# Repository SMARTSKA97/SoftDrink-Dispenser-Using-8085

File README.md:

# SoftDrink-Dispenser-Using-8085
## Objective:
The basic idea of the automated Softdrink dispenser is that it allows the user to select one out of
three options (small, medium and large) for the amount of liquid as desired.

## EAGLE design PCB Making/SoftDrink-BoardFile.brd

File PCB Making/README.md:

This directory contains the construction of PCB using EAGLE Autodesk free version.
## Board Size
### Width = 
6.02 inches
### Height = 
3.85 inches

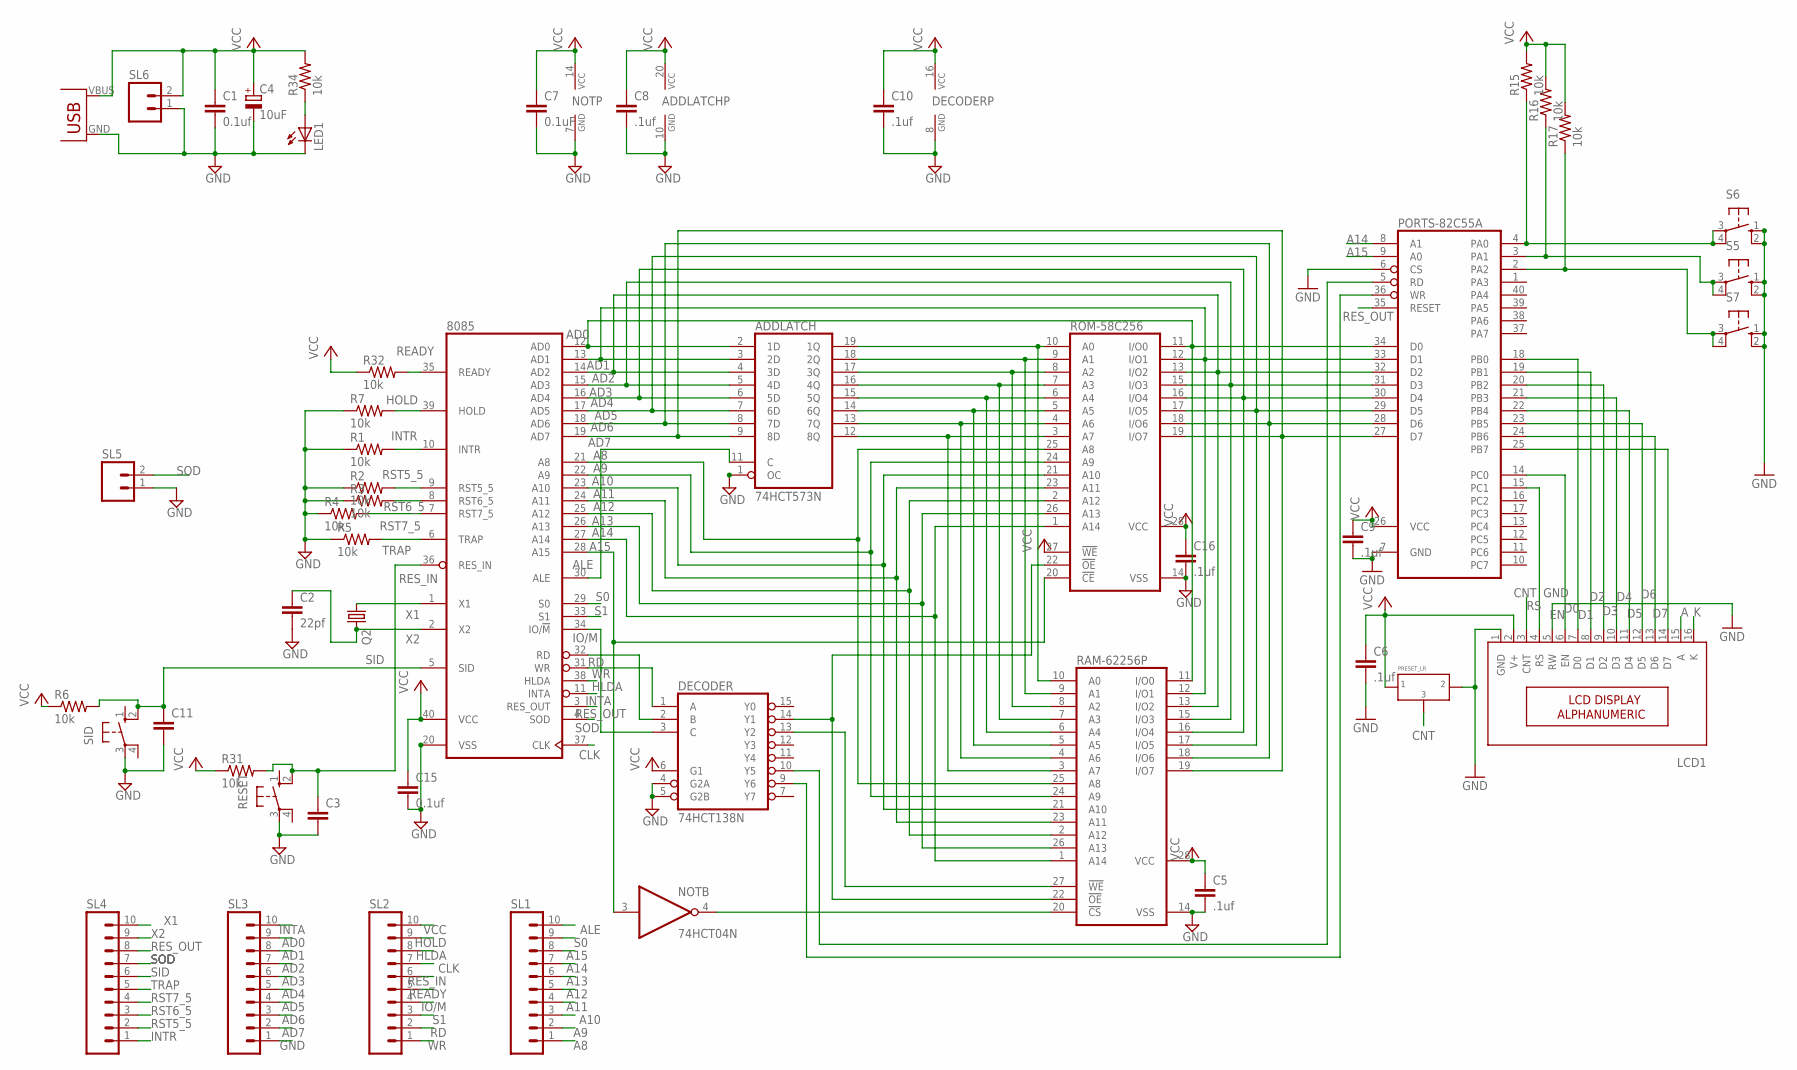
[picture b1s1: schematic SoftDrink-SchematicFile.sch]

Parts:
8085: 8085; DIL40
ADDLATCH: 74HCT573N; DIL20
C1, C15: 0.1uf; C025-024X044
C2: 22pf; C025-024X044
C3, C11: C-EU025-025X050; C025-025X050
C4: 10uF; E5-8,5
C5, C6, C8, C9, C10, C16: .1uf; C025-024X044
C7: 0.1uF; C025-024X044
DECODER: 74HCT138N; DIL16
LCD1: 16X2LCD; 16X2_LCD
LED1: LED5MM
NOT: 74HCT04N; DIL14
PORTS-82C55A: 82C55A; DIL40
Q2: CRYSTALHC49US; HC49US
R1, R2, R3, R4, R5, R6, R7, R15, R16, R17, R31, R32, R34: 10k; 0207/7
RAM-62256P: 62256P; DIL28-6
RESET: 10-XX; B3F-10XX
ROM-58C256: 58C256P; DIL28-6
S5, S6, S7: 10-XX; B3F-10XX
SID: 10-XX; B3F-10XX
SL1, SL2, SL3, SL4: M10; 10P
SL5, SL6: M02; 02P
U$2: USB(POWER)
U$3: PRESET_LR

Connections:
A: LCD1.15 (A)
A8: 8085.21 (A8), RAM-62256P.25 (A8), ROM-58C256.25 (A8), SL1.1
A9: 8085.22 (A9), RAM-62256P.24 (A9), ROM-58C256.24 (A9), SL1.2
A10: 8085.23 (A10), RAM-62256P.21 (A10), ROM-58C256.21 (A10), SL1.3
A11: 8085.24 (A11), RAM-62256P.23 (A11), ROM-58C256.23 (A11), SL1.4
A12: 8085.25 (A12), RAM-62256P.2 (A12), ROM-58C256.2 (A12), SL1.5
A13: 8085.26 (A13), RAM-62256P.26 (A13), ROM-58C256.26 (A13), SL1.6
A14: 8085.27 (A14), PORTS-82C55A.8 (A1), RAM-62256P.1 (A14), ROM-58C256.1 (A14), SL1.7
A15: 8085.28 (A15), NOT.3 (I), PORTS-82C55A.9 (A0), ROM-58C256.20 (!CE), SL1.8
AD0: 8085.12 (AD0), ADDLATCH.2 (1D), PORTS-82C55A.34 (D0), RAM-62256P.11 (I/O0), ROM-58C256.11 (I/O0), SL3.9
AD1: 8085.13 (AD1), ADDLATCH.3 (2D), PORTS-82C55A.33 (D1), RAM-62256P.12 (I/O1), ROM-58C256.12 (I/O1), SL3.8
AD2: 8085.14 (AD2), ADDLATCH.4 (3D), PORTS-82C55A.32 (D2), RAM-62256P.13 (I/O2), ROM-58C256.13 (I/O2), SL3.7
AD3: 8085.15 (AD3), ADDLATCH.5 (4D), PORTS-82C55A.31 (D3), RAM-62256P.15 (I/O3), ROM-58C256.15 (I/O3), SL3.6
AD4: 8085.16 (AD4), ADDLATCH.6 (5D), PORTS-82C55A.30 (D4), RAM-62256P.16 (I/O4), ROM-58C256.16 (I/O4), SL3.5
AD5: 8085.17 (AD5), ADDLATCH.7 (6D), PORTS-82C55A.29 (D5), RAM-62256P.17 (I/O5), ROM-58C256.17 (I/O5), SL3.4
AD6: 8085.18 (AD6), ADDLATCH.8 (7D), PORTS-82C55A.28 (D6), RAM-62256P.18 (I/O6), ROM-58C256.18 (I/O6), SL3.3
AD7: 8085.19 (AD7), ADDLATCH.9 (8D), PORTS-82C55A.27 (D7), RAM-62256P.19 (I/O7), ROM-58C256.19 (I/O7), SL3.2
ALE: 8085.30 (ALE), ADDLATCH.11 (C), SL1.10
CLK: 8085.37 (CLK), SL2.7
CNT: LCD1.3 (CNT), U$3.P$3 (3)
D0: LCD1.7 (D0), PORTS-82C55A.18 (PB0)
D1: LCD1.8 (D1), PORTS-82C55A.19 (PB1)
D2: LCD1.9 (D2), PORTS-82C55A.20 (PB2)
D3: LCD1.10 (D3), PORTS-82C55A.21 (PB3)
D4: LCD1.11 (D4), PORTS-82C55A.22 (PB4)
D5: LCD1.12 (D5), PORTS-82C55A.23 (PB5)
D6: LCD1.13 (D6), PORTS-82C55A.24 (PB6)
D7: LCD1.14 (D7), PORTS-82C55A.25 (PB7)
EN: LCD1.6 (EN), PORTS-82C55A.14 (PC0)
GND: 8085.20 (VSS), ADDLATCH.1 (OC), ADDLATCH.10 (GND), C1.2, C2.2, C3.2, C4.-, C5.2, C6.2, C7.2, C8.2, C9.2, C10.2, C11.2, C15.2, C16.2, DECODER.4 (G2A), DECODER.5 (G2B), DECODER.8 (GND), LCD1.1 (GND), LCD1.5 (RW), LED1.K (C), NOT.7 (GND), PORTS-82C55A.6 (CS), PORTS-82C55A.7 (GND), R1.1, R2.1, R3.1, R4.1, R5.1, R7.1, RAM-62256P.14 (VSS), RESET.3, ROM-58C256.14 (VSS), S5.1 (S), S5.2 (S1), S6.1 (S), S6.2 (S1), S7.1 (S), S7.2 (S1), SID.3, SL3.1, SL5.1, SL6.1, U$2.GND, U$3.P$2 (2)
HLDA: 8085.38 (HLDA), SL2.8
HOLD: 8085.39 (HOLD), R7.2, SL2.9
INTA: 8085.11 (INTA), SL3.10
INTR: 8085.10 (INTR), R1.2, SL4.1
IO/M: 8085.34 (IO/!M), DECODER.3 (C), SL2.4
K: LCD1.16 (K)
unnamed: ADDLATCH.19 (1Q), RAM-62256P.10 (A0), ROM-58C256.10 (A0)
unnamed: ADDLATCH.18 (2Q), RAM-62256P.9 (A1), ROM-58C256.9 (A1)
unnamed: ADDLATCH.17 (3Q), RAM-62256P.8 (A2), ROM-58C256.8 (A2)
unnamed: ADDLATCH.16 (4Q), RAM-62256P.7 (A3), ROM-58C256.7 (A3)
unnamed: ADDLATCH.15 (5Q), RAM-62256P.6 (A4), ROM-58C256.6 (A4)
unnamed: ADDLATCH.14 (6Q), RAM-62256P.5 (A5), ROM-58C256.5 (A5)
unnamed: ADDLATCH.13 (7Q), RAM-62256P.4 (A6), ROM-58C256.4 (A6)
unnamed: ADDLATCH.12 (8Q), RAM-62256P.3 (A7), ROM-58C256.3 (A7)
unnamed: DECODER.9 (Y6), PORTS-82C55A.36 (WR)
unnamed: LED1.A, R34.1
unnamed: PORTS-82C55A.4 (PA0), R15.1, S6.3, S6.4 (P1)
unnamed: PORTS-82C55A.2 (PA2), R17.1, S7.3, S7.4 (P1)
unnamed: PORTS-82C55A.3 (PA1), R16.1, S5.3, S5.4 (P1)
unnamed: DECODER.14 (Y1), RAM-62256P.22 (!OE), ROM-58C256.22 (!OE)
unnamed: DECODER.13 (Y2), RAM-62256P.27 (!WE)
unnamed: NOT.4 (O), RAM-62256P.20 (!CS)
unnamed: DECODER.10 (Y5), PORTS-82C55A.5 (RD)
RD: 8085.32 (RD), DECODER.2 (B), SL2.2
READY: 8085.35 (READY), R32.2, SL2.5
RES_IN: 8085.36 (RES_IN), C3.1, R31.2, RESET.2 (S1), SL2.6
RES_OUT: 8085.3 (RES_OUT), PORTS-82C55A.35 (RESET), SL4.8
RS: LCD1.4 (RS), PORTS-82C55A.15 (PC1)
RST5_5: 8085.9 (RST5_5), R2.2, SL4.2
RST6_5: 8085.8 (RST6_5), R3.2, SL4.3
RST7_5: 8085.7 (RST7_5), R4.2, SL4.4
S0: 8085.29 (S0), SL1.9
S1: 8085.33 (S1), SL2.3
SID: 8085.5 (SID), C11.1, R6.2, SID.2 (S1), SL4.6
SOD: 8085.4 (SOD), SL4.7, SL5.2
TRAP: 8085.6 (TRAP), R5.2, SL4.5
VCC: 8085.40 (VCC), ADDLATCH.20 (VCC), C1.1, C4.+, C5.1, C6.1, C7.1, C8.1, C9.1, C10.1, C15.1, C16.1, DECODER.6 (G1), DECODER.16 (VCC), LCD1.2 (V+), NOT.14 (VCC), PORTS-82C55A.26 (VCC), R6.1, R15.2, R16.2, R17.2, R31.1, R32.1, R34.2, RAM-62256P.28 (VCC), ROM-58C256.27 (!WE), ROM-58C256.28 (VCC), SL2.10, SL6.2, U$2.VBUS (VCC), U$3.P$1 (1)
WR: 8085.31 (WR), DECODER.1 (A), SL2.1
X1: 8085.1 (X1), Q2.1, SL4.10
X2: 8085.2 (X2), C2.1, Q2.2, SL4.9

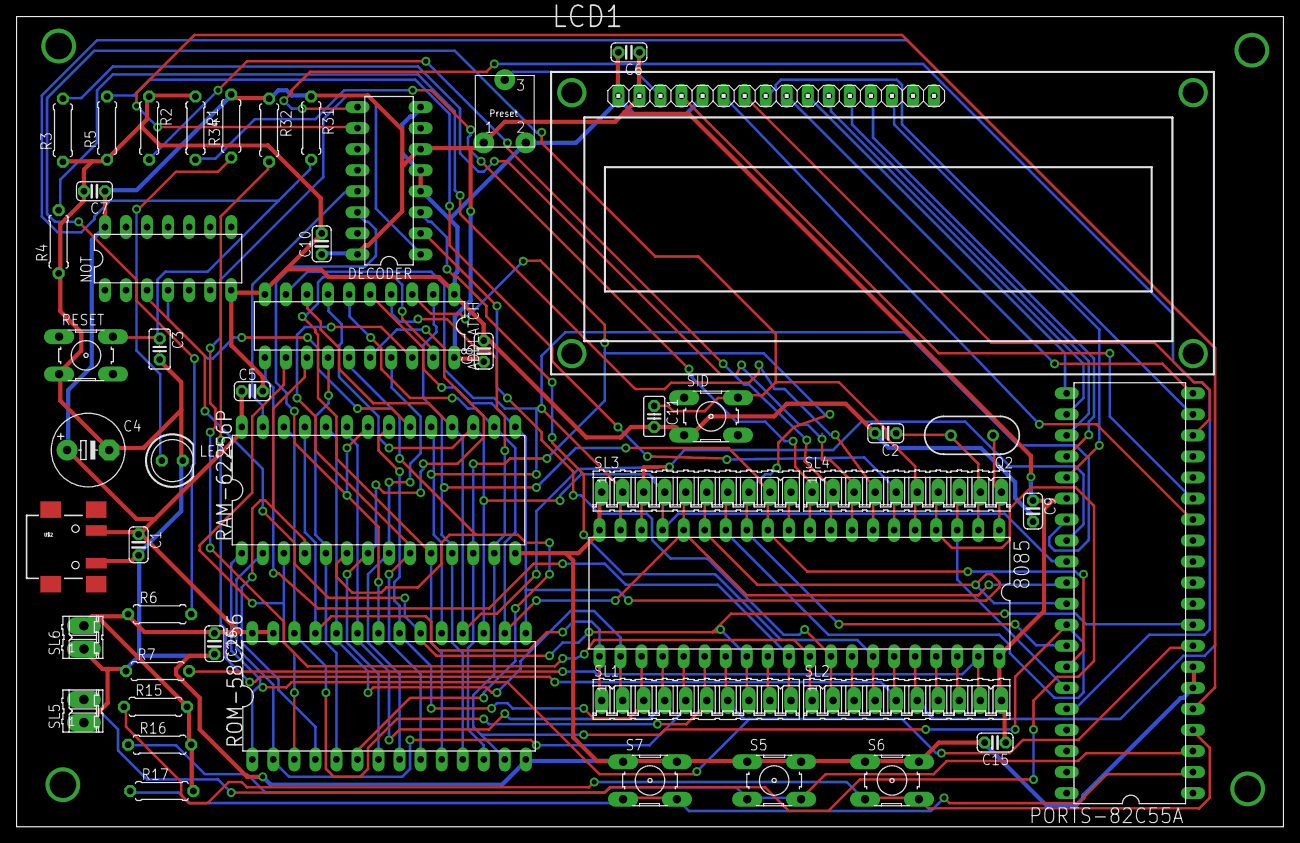
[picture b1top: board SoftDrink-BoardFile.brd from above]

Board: 2 copper layers, 152.9 x 97.8 mm, 49 parts (0 on the bottom side), 68 nets.

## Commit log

2019-01-17 Rename Readme to README.md
2019-01-17 Rename Readme.md to README.md
2019-01-17 Create Front-Of-PCB
2019-01-17 Add files via upload
    Updated Image
2019-01-17 Add files via upload
    Front side of PCB
2019-01-17 Add files via upload
    Drill of the PCB.
2019-01-17 Add files via upload
    Updated Board
2019-01-17 Create 8085_Mnemonic_Codes
    Updated 17-01-2019
2019-01-17 Update 8085_Mnemonic_Codes
    Specific Changes
2019-01-17 Update README.md
    Updated Objective
2019-01-17 Update README.md
    Designing the README.md
